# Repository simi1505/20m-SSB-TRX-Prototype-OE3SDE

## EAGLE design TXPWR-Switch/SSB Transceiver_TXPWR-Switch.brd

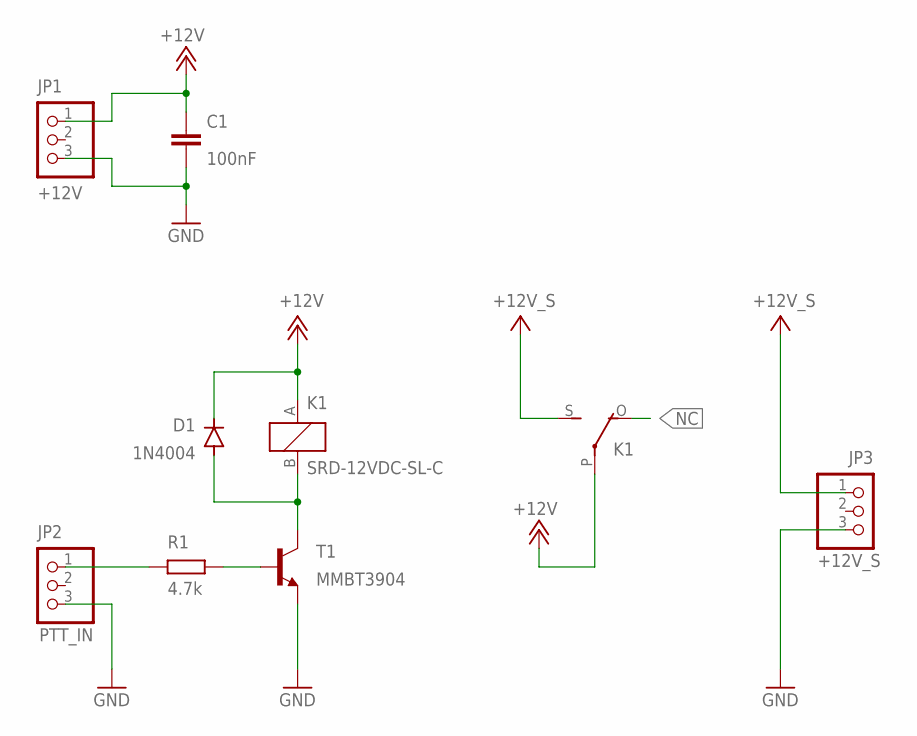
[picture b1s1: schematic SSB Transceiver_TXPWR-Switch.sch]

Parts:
C1: 100nF; C0805K
D1: 1N4004; DO41-10
JP1: +12V; 1X03
JP2: PTT_IN; 1X03
JP3: +12V_S; 1X03
K1: SRD-12VDC-SL-C
R1: 4.7k; R0805
T1: MMBT3904; SOT23-BEC

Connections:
+12V: C1.1, D1.C, JP1.1, K1.A, K1.P
+12V_S: JP3.1, K1.S
GND: C1.2, JP1.3, JP2.3, JP3.3, T1.E
unnamed: R1.2, T1.B
unnamed: D1.A, K1.B, T1.C
unnamed: JP2.1, R1.1
NC: K1.O

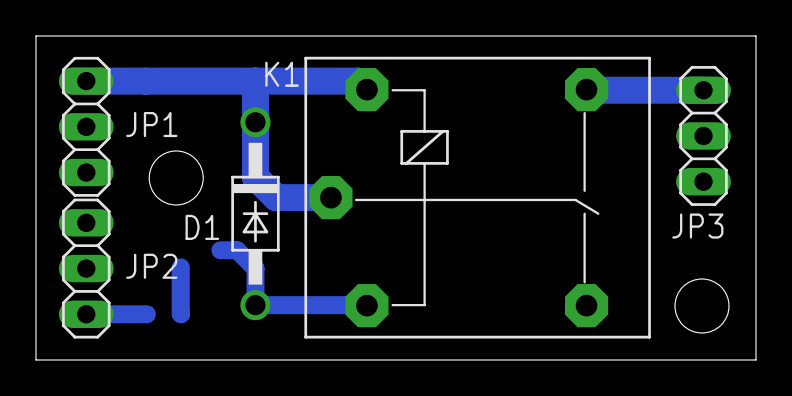
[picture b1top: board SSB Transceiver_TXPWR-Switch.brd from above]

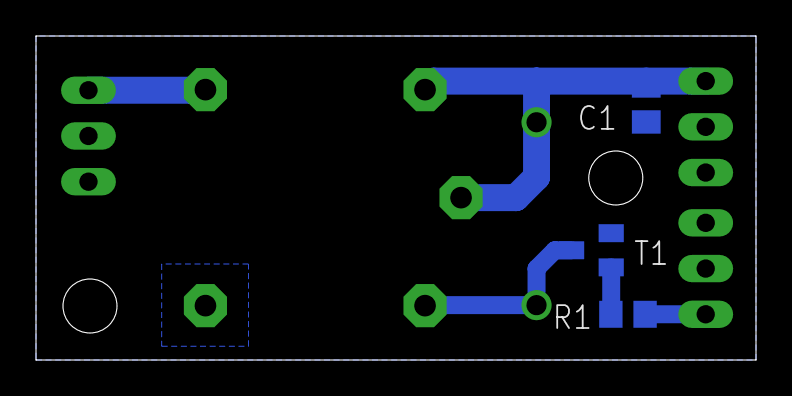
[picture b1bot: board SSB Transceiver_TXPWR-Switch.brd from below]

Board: 2 copper layers, 40.0 x 18.0 mm, 8 parts (3 on the bottom side), 6 nets.

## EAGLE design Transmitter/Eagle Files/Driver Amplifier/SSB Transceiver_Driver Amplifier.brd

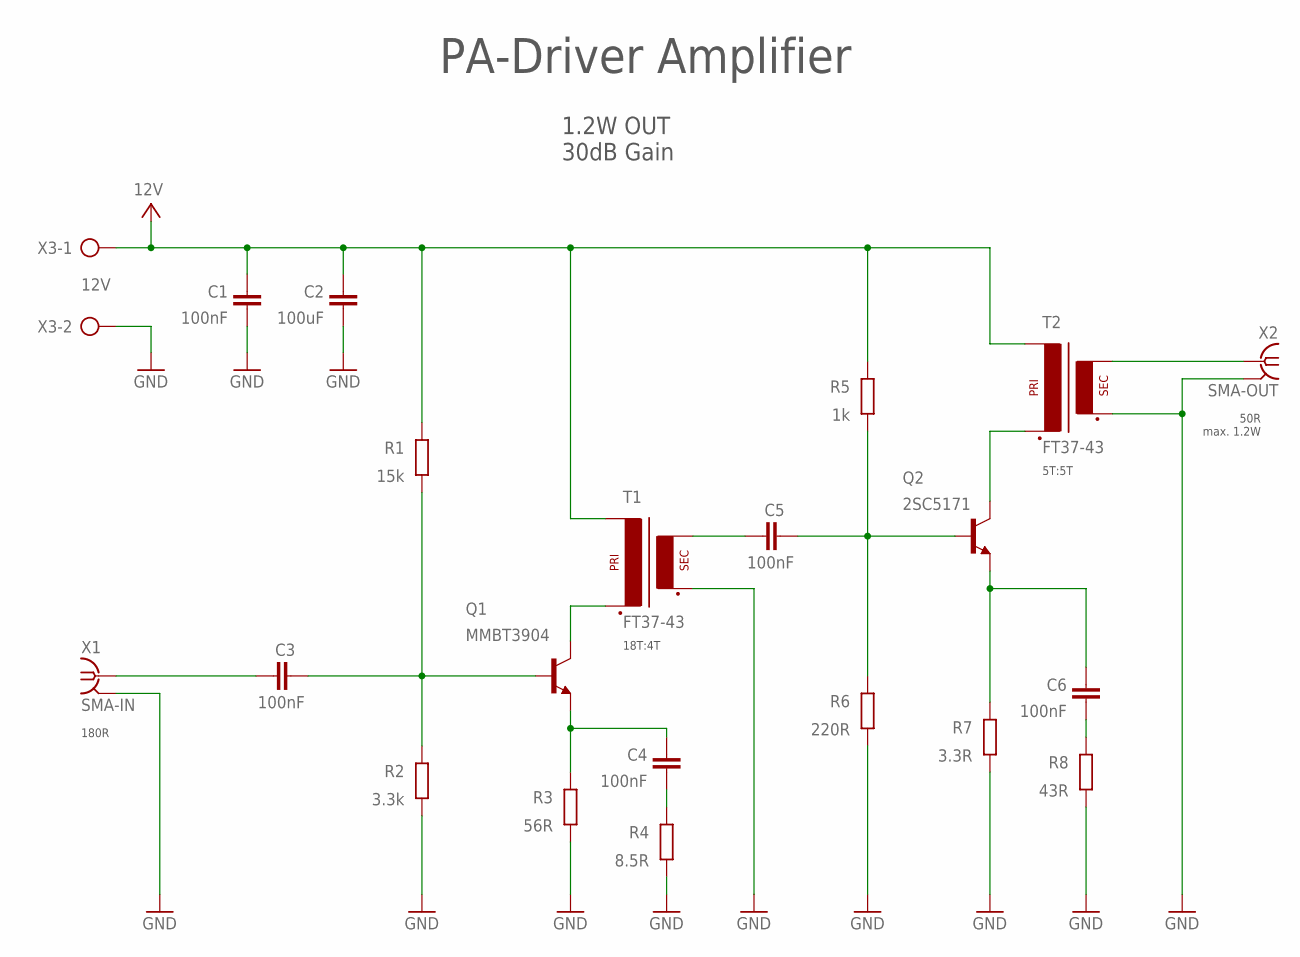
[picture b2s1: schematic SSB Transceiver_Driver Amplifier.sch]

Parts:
C1, C3, C4, C5, C6: 100nF; C0805
C2: 100uF; C0805
Q1: MMBT3904; SOT23-BEC
Q2: 2SC5171; TO220
R1: 15k; R0805
R2: 3.3k; R0805
R3: 56R; R0805
R4: 8.5R; R0805
R5: 1k; R0805
R6: 220R; R0805
R7: 3.3R; R0805
R8: 43R; R0805
T1, T2: FT37-43; FT37-43SMD
X1: SMA-IN; J502-ND-142-0711-821/826
X2: SMA-OUT; J502-ND-142-0711-821/826
X3: 12V; AK300/2

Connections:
GND: C1.1, C2.1, R2.2, R3.1, R4.1, R6.1, R7.1, R8.1, T1.S$2 (S2), T2.S$2 (S2), X1.G@1 (2), X1.G@2 (2), X1.G@3 (2), X1.G@4 (2), X2.G@1 (2), X2.G@2 (2), X2.G@3 (2), X2.G@4 (2), X3.2
unnamed: Q1.C, T1.P$2 (P2)
unnamed: T2.S$1 (S1), X2.1
unnamed: Q2.2 (C), T2.P$2 (P2)
unnamed: C4.2, Q1.E, R3.2
unnamed: C4.1, R4.2
unnamed: C3.1, Q1.B, R1.2, R2.1
unnamed: C3.2, X1.1
unnamed: C5.1, Q2.1 (B), R5.1, R6.2
unnamed: C6.2, Q2.3 (E), R7.2
unnamed: C5.2, T1.S$1 (S1)
unnamed: C6.1, R8.2
VCC: C1.2, C2.2, R1.1, R5.2, T1.P$1 (P1), T2.P$1 (P1), X3.1

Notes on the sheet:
50R max. 1.2W
180R
PA-Driver Amplifier
1.2W OUT 30dB Gain
5T:5T
18T:4T

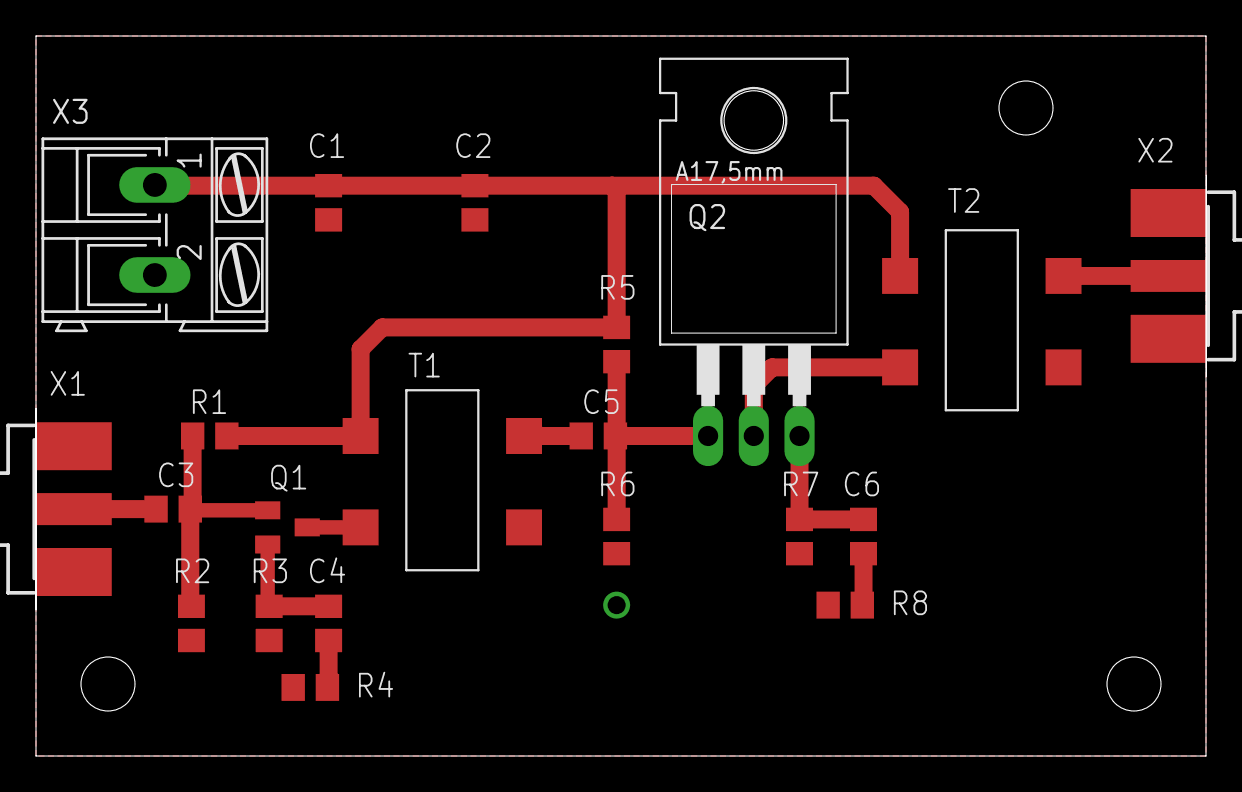
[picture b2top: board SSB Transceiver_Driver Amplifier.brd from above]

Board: 2 copper layers, 65.0 x 40.0 mm, 21 parts (0 on the bottom side), 13 nets.

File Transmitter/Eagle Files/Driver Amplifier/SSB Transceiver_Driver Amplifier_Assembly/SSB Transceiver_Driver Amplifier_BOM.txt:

Partlist exported from E:/Simon Dorrer/DIY Projekte/Amateurfunkprojekte/SSB Transceiver/Transmitter/Eagle Files/Driver Amplifier/SSB Transceiver_Driver Amplifier.sch at 08/02/2020 14:05

Qty Value    Device                      Package                  Parts              Description                                                MF                 MPN          OC_FARNELL OC_NEWARK POPULARITY SPICEPREFIX
5   100nF    C-EUC0805                   C0805                    C1, C3, C4, C5, C6 CAPACITOR, European symbol                                                                                      88         C          
1   100uF    C-EUC0805                   C0805                    C2                 CAPACITOR, European symbol                                                                                      88         C          
1   12V      AK300/2                     AK300/2                  X3                 CONNECTOR                                                                                  unknown    unknown                         
1   15k      R-EU_R0805                  R0805                    R1                 RESISTOR, European symbol                                                                                       86         R          
1   1k       R-EU_R0805                  R0805                    R5                 RESISTOR, European symbol                                                                                       86         R          
1   220R     R-EU_R0805                  R0805                    R6                 RESISTOR, European symbol                                                                                       86         R          
1   2SC5171  TIP31B                      TO220                    Q2                 NPN Transistor  Medium Power Linear Switching Applications                                                                            
1   3.3R     R-EU_R0805                  R0805                    R7                 RESISTOR, European symbol                                                                                       86         R          
1   3.3k     R-EU_R0805                  R0805                    R2                 RESISTOR, European symbol                                                                                       86         R          
1   43R      R-EU_R0805                  R0805                    R8                 RESISTOR, European symbol                                                                                       86         R          
1   56R      R-EU_R0805                  R0805                    R3                 RESISTOR, European symbol                                                                                       86         R          
1   8.5R     R-EU_R0805                  R0805                    R4                 RESISTOR, European symbol                                                                                       86         R          
2   FT37-43  FT37-43                     FT37-43SMD               T1, T2                                                                                                                                                   
1   MMBT3904 MMBT3904LT1-NPN-SOT23-BEC   SOT23-BEC                Q1                 NPN Transistror                                                                                                                       
1   SMA-IN   SMA-PCB-CON142-0711-821/826 J502-ND-142-0711-821/826 X1                 SMA 50 Ohm End Launch Jack Receptacle - Round Contact      JOHNSON COMPONENTS 142-0711-821 1019328    16F3627                         
1   SMA-OUT  SMA-PCB-CON142-0711-821/826 J502-ND-142-0711-821/826 X2                 SMA 50 Ohm End Launch Jack Receptacle - Round Contact      JOHNSON COMPONENTS 142-0711-821 1019328    16F3627

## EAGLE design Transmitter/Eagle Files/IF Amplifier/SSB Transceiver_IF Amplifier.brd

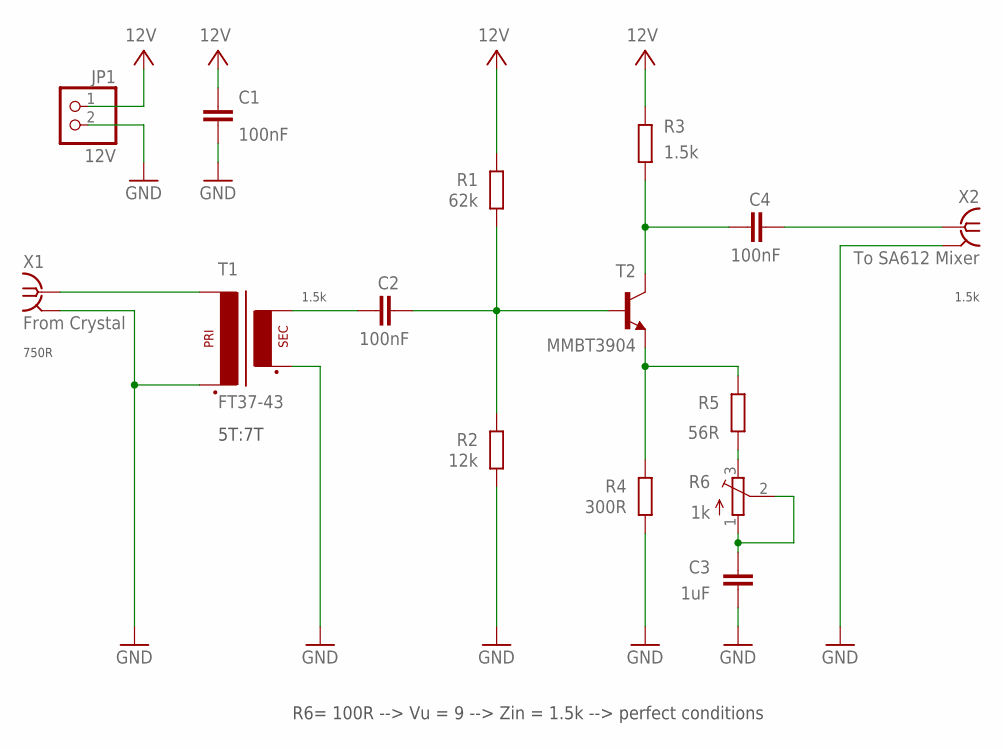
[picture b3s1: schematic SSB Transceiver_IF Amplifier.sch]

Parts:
C1, C2, C4: 100nF; C0805
C3: 1uF; C0805
JP1: 12V; 1X02
R1: 62k; R0805
R2: 12k; R0805
R3: 1.5k; R0805
R4: 300R; R0805
R5: 56R; R0805
R6: 1k; 3223G
T1: FT37-43; FT37-43SMD
T2: MMBT3904; SOT23-BEC
X1: From Crystal; J502-ND-142-0711-821/826
X2: To SA612 Mixer; J502-ND-142-0711-821/826

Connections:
GND: C1.1, C3.1, JP1.2, R2.2, R4.2, T1.P$2 (P2), T1.S$2 (S2), X1.G@1 (2), X1.G@2 (2), X1.G@3 (2), X1.G@4 (2), X2.G@1 (2), X2.G@2 (2), X2.G@3 (2), X2.G@4 (2)
unnamed: R4.1, R5.1, T2.E
unnamed: C3.2, R6.1 (A), R6.2 (S)
unnamed: C4.1, R3.2, T2.C
unnamed: T1.P$1 (P1), X1.1
unnamed: C2.2, R1.2, R2.1, T2.B
unnamed: C4.2, X2.1
unnamed: C2.1, T1.S$1 (S1)
unnamed: R5.2, R6.3 (E)
VCC: C1.2, JP1.1, R1.1, R3.1

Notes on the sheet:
750R
1.5k
5T:7T
R6= 100R --> Vu = 9 --> Zin = 1.5k --> perfect conditions

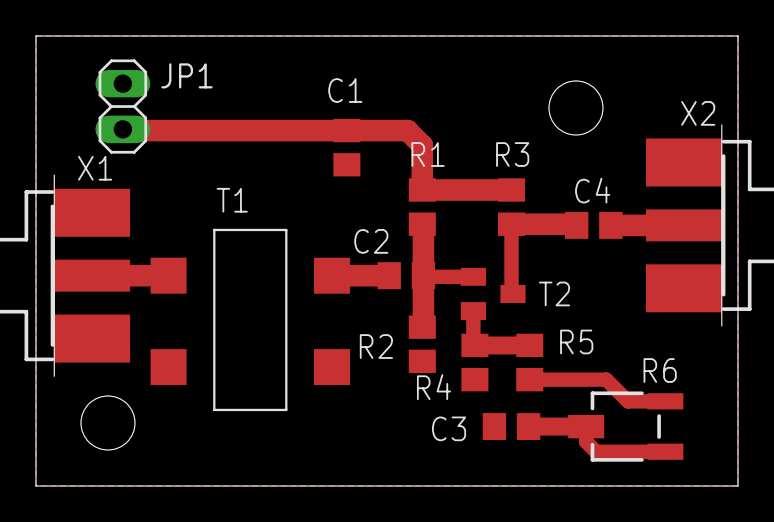
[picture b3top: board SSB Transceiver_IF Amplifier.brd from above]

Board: 2 copper layers, 39.0 x 25.0 mm, 15 parts (0 on the bottom side), 10 nets.

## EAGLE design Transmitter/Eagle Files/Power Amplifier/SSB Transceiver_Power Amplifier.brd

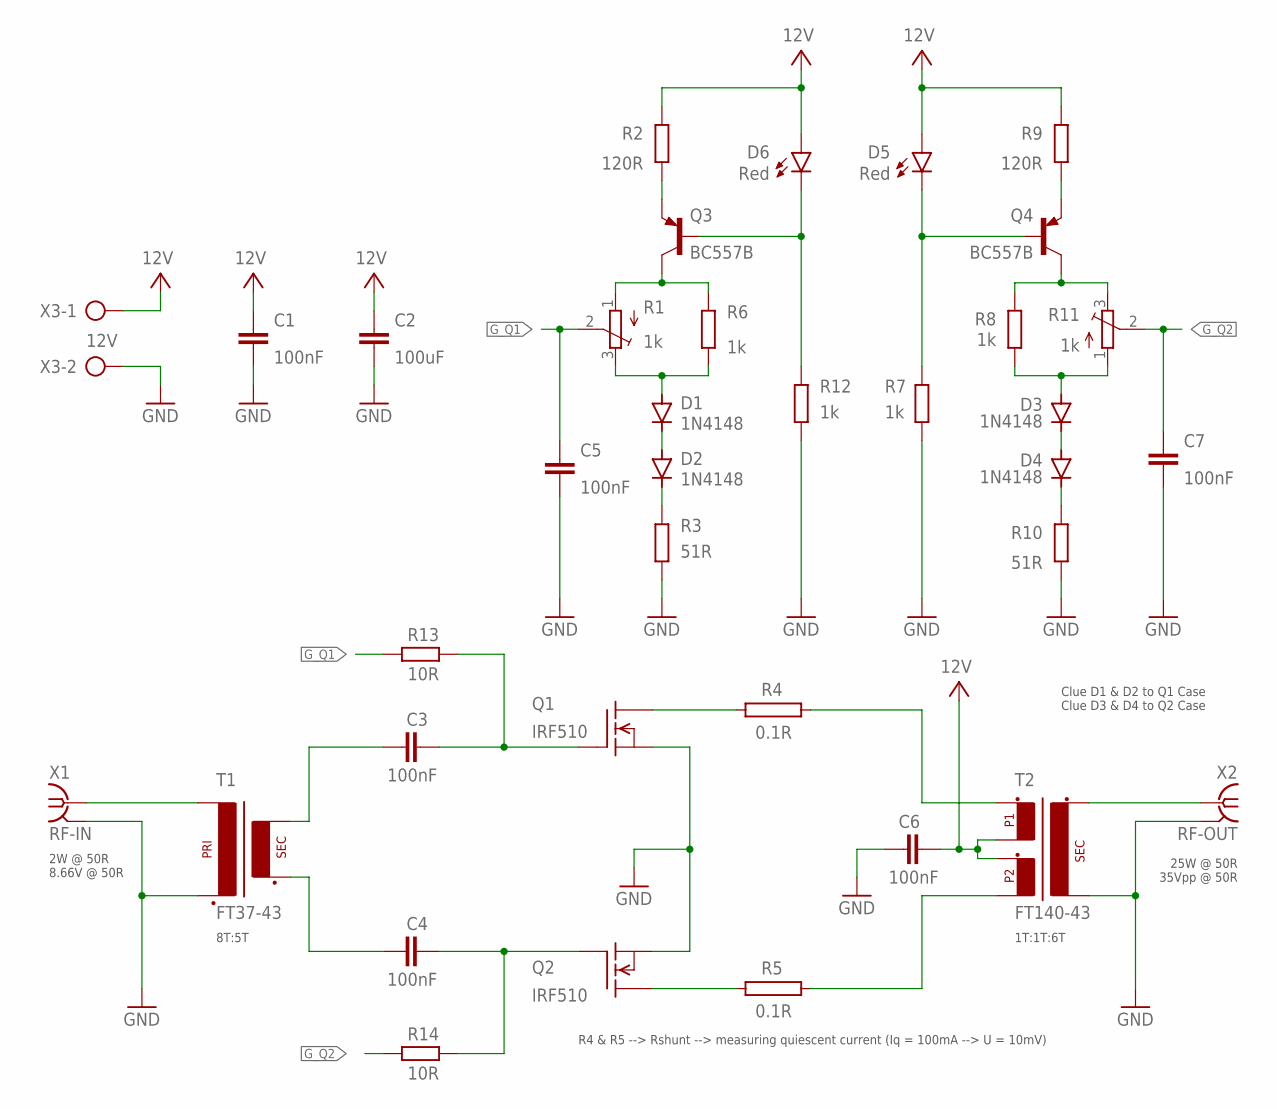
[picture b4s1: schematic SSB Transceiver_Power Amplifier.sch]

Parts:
C1, C3, C4, C5, C6, C7: 100nF; C0805
C2: 100uF; C0805
D1, D2, D3, D4: 1N4148; SOD323-W
D5, D6: Red; CHIP-LED0805
Q1, Q2: IRF510; TO220
Q3, Q4: BC557B; TO92-EBC
R1, R11: 1k; 3223G
R2, R9: 120R; R0805
R3, R10: 51R; R0805
R4, R5: 0.1R; MNS-5
R6, R7, R8, R12: 1k; R0805
R13, R14: 10R; R0805
T1: FT37-43; FT37-43SMD
T2: FT140-43; FT37-43CENTERTAPSMD
X1: RF-IN; J502-ND-142-0711-821/826
X2: RF-OUT; J502-ND-142-0711-821/826
X3: 12V; AK300/2

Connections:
GND: C1.1, C2.1, C5.1, C6.1, C7.1, Q1.3 (S), Q2.3 (S), R3.1, R7.1, R10.1, R12.1, T1.P$2 (P2), T2.S$2 (S2), X1.G@1 (2), X1.G@2 (2), X1.G@3 (2), X1.G@4 (2), X2.G@1 (2), X2.G@2 (2), X2.G@3 (2), X2.G@4 (2), X3.2
G_Q1: C5.2, R1.2 (S), R13.2
G_Q2: C7.2, R11.2 (S), R14.2
unnamed: C3.2, T1.S$1 (S1)
unnamed: C4.2, T1.S$2 (S2)
unnamed: T1.P$1 (P1), X1.1
unnamed: Q4.C, R8.2, R11.3 (E)
unnamed: Q3.E, R2.1
unnamed: R4.1, T2.P$1 (P1_1)
unnamed: D3.A, R8.1, R11.1 (A)
unnamed: R5.2, T2.P$4 (P2_2)
unnamed: Q1.2 (D), R4.2
unnamed: T2.S$1 (S1), X2.1
unnamed: Q2.2 (D), R5.1
unnamed: D5.C, Q4.B, R7.2
unnamed: D3.C, D4.A
unnamed: Q4.E, R9.1
unnamed: Q3.C, R1.1 (A), R6.2
unnamed: D1.C, D2.A
unnamed: D1.A, R1.3 (E), R6.1
unnamed: D2.C, R3.2
unnamed: D4.C, R10.2
unnamed: D6.C, Q3.B, R12.2
unnamed: C3.1, Q1.1 (G), R13.1
unnamed: C4.1, Q2.1 (G), R14.1
VCC: C1.2, C2.2, C6.2, D5.A, D6.A, R2.2, R9.2, T2.P$2 (P1_2), T2.P$3 (P2_1), X3.1

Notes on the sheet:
2W @ 50R 8.66V @ 50R
25W @ 50R 35Vpp @ 50R
Clue D1 & D2 to Q1 Case Clue D3 & D4 to Q2 Case
1T:1T:6T
8T:5T
R4 & R5 --> Rshunt --> measuring quiescent current (Iq = 100mA --> U = 10mV)

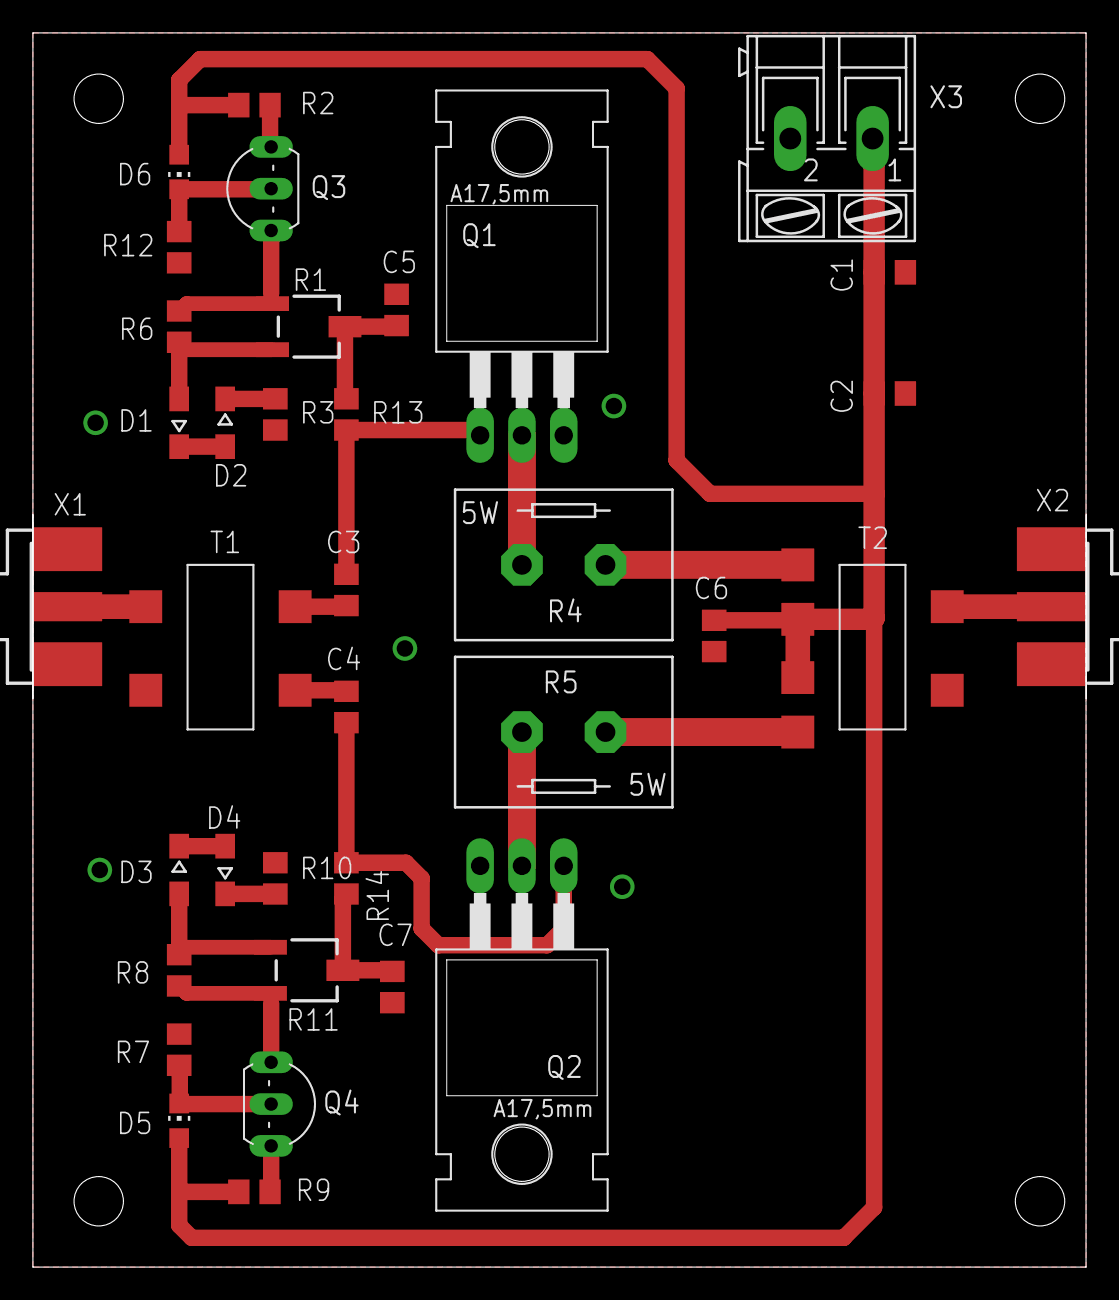
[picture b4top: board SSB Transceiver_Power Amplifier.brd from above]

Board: 2 copper layers, 64.0 x 75.0 mm, 36 parts (0 on the bottom side), 26 nets.

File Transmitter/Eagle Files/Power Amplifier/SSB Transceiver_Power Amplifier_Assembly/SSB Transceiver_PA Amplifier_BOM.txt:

Partlist exported from E:/Simon Dorrer/DIY Projekte/Amateurfunkprojekte/SSB Transceiver/Transmitter/Eagle Files/PA Amplifier/SSB Transceiver_PA Amplifier.sch at 04/02/2020 20:22

Qty Value    Device                      Package                  Parts                  Description                                                MF                 MPN          OC_FARNELL OC_NEWARK POPULARITY SPICEPREFIX
2   0.1R     RMNS-5                      MNS-5                    R4, R5                 Power Resitor                                                                              unknown    unknown                         
6   100nF    C-EUC0805                   C0805                    C1, C3, C4, C5, C6, C7 CAPACITOR, European symbol                                                                                      88         C          
1   100uF    C-EUC0805                   C0805                    C2                     CAPACITOR, European symbol                                                                                      88         C          
2   10R      R-EU_R0805                  R0805                    R13, R14               RESISTOR, European symbol                                                                                       86         R          
2   120R     R-EU_R0805                  R0805                    R2, R9                 RESISTOR, European symbol                                                                                       86         R          
1   12V      AK300/2                     AK300/2                  X3                     CONNECTOR                                                                                  unknown    unknown                         
4   1N4148   DIODE-SOD323-W              SOD323-W                 D1, D2, D3, D4         DIODE                                                                                                                                 
4   1k       R-EU_R0805                  R0805                    R6, R7, R8, R12        RESISTOR, European symbol                                                                                       86         R          
2   1k       TRIM_EU-3223G               3223G                    R1, R11                POTENTIOMETER                                                                                                                         
2   51R      R-EU_R0805                  R0805                    R3, R10                RESISTOR, European symbol                                                                                       86         R          
2   BC557B   BC557B                      TO92-EBC                 Q3, Q4                 PNP Transistror                                                                                                                       
1   FT140-43 FT37-43CENTERTAP            FT37-43CENTERTAPSMD      T2                                                                                                                                                           
1   FT37-43  FT37-43                     FT37-43SMD               T1                                                                                                                                                           
2   IRF510   IRF510                      TO220                    Q1, Q2                 N-Channel Enhancement MOSFET (HEXFET); 100V; 5,6A; 0,54Ohm                                                                            
1   RF-IN    SMA-PCB-CON142-0711-821/826 J502-ND-142-0711-821/826 X1                     SMA 50 Ohm End Launch Jack Receptacle - Round Contact      JOHNSON COMPONENTS 142-0711-821 1019328    16F3627                         
1   RF-OUT   SMA-PCB-CON142-0711-821/826 J502-ND-142-0711-821/826 X2                     SMA 50 Ohm End Launch Jack Receptacle - Round Contact      JOHNSON COMPONENTS 142-0711-821 1019328    16F3627                         
2   Red      LEDCHIP-LED0805             CHIP-LED0805             D5, D6                 LED

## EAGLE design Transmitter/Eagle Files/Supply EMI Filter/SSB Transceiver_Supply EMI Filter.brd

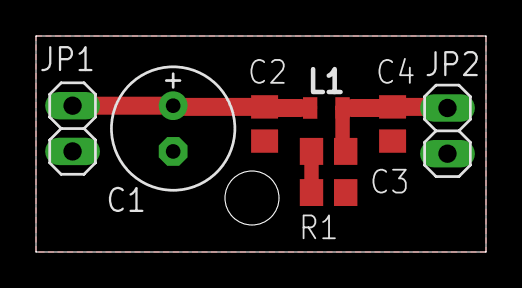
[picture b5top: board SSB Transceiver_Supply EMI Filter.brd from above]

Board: 2 copper layers, 25.0 x 12.0 mm, 8 parts (0 on the bottom side), 4 nets.

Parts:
C1: 100uF; E2,5-7
C2, C4: 10nF; C0805
C3: 10uF; C0805
JP1: 12V; 1X02
JP2: 12V_filtered; 1X02
L1: BLM21SP102SH1D; 0805
R1: 10R; R0805

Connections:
+12V: C1.+, C2.1, JP1.2, L1.1
+24V: C3.1, C4.1, JP2.1, L1.2
GND: C1.-, C2.2, C4.2, JP1.1, JP2.2, R1.1
unnamed: C3.2, R1.2

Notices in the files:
parts and their libraries:
SparkFun-Coils: Licensing: Creative Commons ShareAlike 4.0 International - https://creativecommons.org/licenses/by-sa/4.0
